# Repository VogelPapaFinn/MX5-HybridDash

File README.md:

# MX5-HybridDash (v2)

A hybrid instrument cluster for a *Mazda MX-5 NB*, which replaces the three small analog gauges and replaces them with 1.5" IPS displays. The project aims to look like an *OEM+* look and feel without destroying the old charm of the car.

## Hardware

The project consists of four custom made PCBs of two types:
- A big Sensor PCB which sits on the back of the cluster, connects to the sensors & ECU and controls the displays
- Three small display PCBs which connect to the displays and receive instructions & data from the Sensor PCB

All four PCBs utilize a powerful ESP32-S3 microcontroller and the CAN bus to communicate with each other. This allows a robust communication without faulty data and provides the possiblity to expand the cluster with new hardware & features in the future-
The displays have a resolution of 360x360 on a 1.5" IPS panel, giving everything a high detailed look.

## Basic Features

Currently the displays can display:
* **RPM**
* **Speed**
* **Indicator (right & left)**
* **Oil Pressure (switch)**
* **Fuel Level**
* **Water Temperature**

This allows for example to calibrate the fuel level sensor so it is more accurate. In my car it shows that the fuel tank is empty when there are 10-15L left. Furthermore due to my size the indicators & the upper scale of the speedometer hide behind the steering wheel. By displaying them in the lower left and right display this isnt an issue anymore.

## Main Feature

My car is a pre-Facelift model and therefore does not have an OBDII connector (at least thats normal here in europe). After a lot of researching, fumbling around, reverse-engineering and testing I managed to establish a **connection** with the **OEM ECU** **without a OBDII connector**. 

At the moment I knowThis of 33 different values that are readable: *(Valus NOT Sensors, as some Sensors output multiple units)*
* **Alternator** - Load (%)
* **Alternator** - Desired Voltage (V)
* **Cabin Fan** - Toggle
* **Brake** - Toggle
* **Rear Window Defroster** - Toggle
* **Daytime Lights** - Toggle
* **Coolant** - Sensor Voltage (V)
* **Coolant** - Temperature (°C)
* **EGR** - Toggle
* **Cooling Fan Speed** - On, Slow Speed
* **Cooling Fan Speed** - On, Medium Speed
* **Cooling Fan Speed** - On, Fast Speed
* **Fuel Pump** - Toggle
* **Injector** - Injection Time (ms)
* **Battery** - Low Voltage (Light Indicator)
* **Headlight Left** - Toggle
* **Headlight Right** - Toggle
* **Idle Bypass** - Time (ms)
* **Idle Switch** - Toggle
* **Engine** - Load (%)
* **Airmass** (V)
* **Airmass** (g/s)
* **Main Relais** - Toggle
* **Engine** - Check Engine Light 
* **Airmass Pre-Cat** - Voltage (V)
* **Power Steering** - Pressure Switch Toggle
* **RPM**
* **EGR** - Valve Position
* **Ignition Timing** - Advancing (°)
* **Immobilizer** - Toggle
* **Throttle** - Voltage (V)
* **ECU** - Input Voltage (V)
* **Speed** (KMH)

## Future Plans
I plan a lot for the project even if its (software wise) stillt at the early beginning. But here is a list of features I aim to implement:
- [ ] Calibration of the sensors
- [ ] Calculation of new Values by combining the hardware & ECU sensors (e.g. current fuel consumption)
- [ ]  Webserver to control the dash
	- [ ] Reading & displaying data from the ECU
- [ ] Customizable display GUI
- [ ] Connection to the smartphone
	- [ ] Google Maps integration / direction notifications in the display GUI
	- [ ] Spotify integration
- [ ] Sensor data tracking & visualization for analyzation (e.g. on track-day use)

Please note that this are just some ideas of mine. This is not a roadmap. This is not organized by priority.

## About me

Hello! Im Finn a 21 year old computer science student from Bonn (Germany). I work as an embedded software engineer (besides my studies of course) and started tinkering around with electronics around two years ago. This project is developed exclusively in my free time for my own fun. I actually started just because I wanted to learn about electronics... Now here I am :)

## Contact

If you have any questions or anything else you are welcome to contact me:
1. Create an issue here in this GitHub repository
2. Contact me via the Miata.net forum. Either via my linked thread or via a [private message](https://forum.miata.net/vb/member.php?u=307577)

## License

The whole project is published under the **GPLv3** license. Basically this means everybody can use, alter and provide the project, free and commercial as long as the provided code and hardware stays open source for the user. Note, that this is my conclusion of the license, before acting please read the license and its terms yourself!!

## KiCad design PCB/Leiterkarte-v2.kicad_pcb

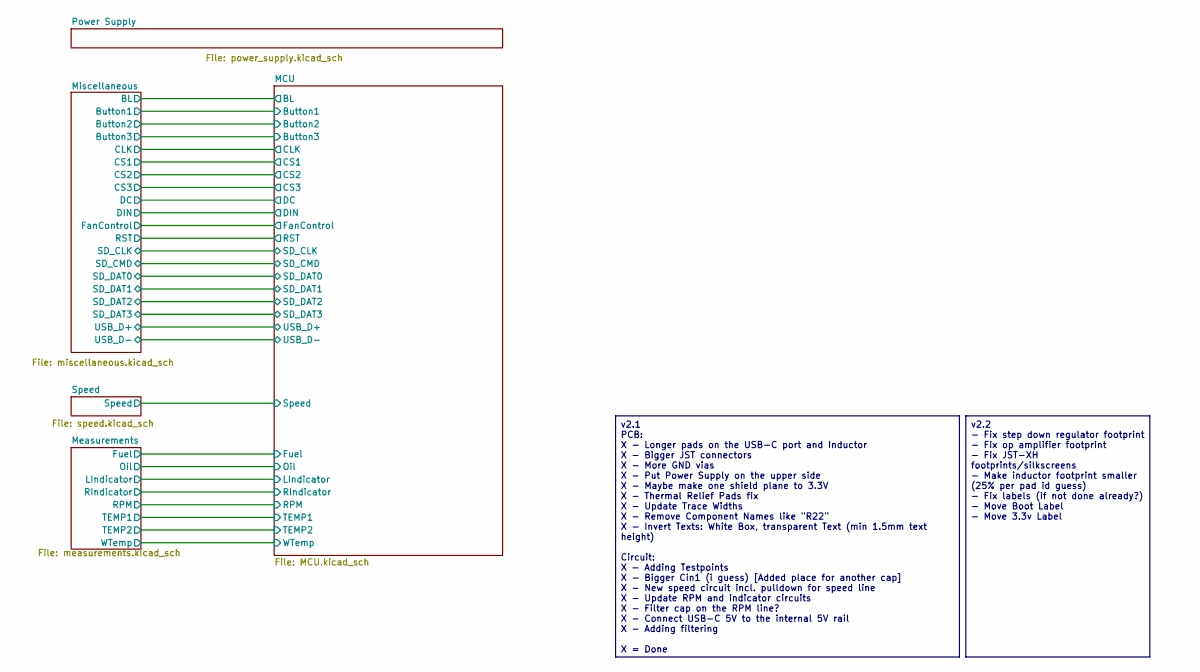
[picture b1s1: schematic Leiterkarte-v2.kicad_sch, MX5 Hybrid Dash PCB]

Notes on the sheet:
v2.2 - Fix step down regulator footprint - Fix op amplifier footprint - Fix JST-XH footprints/silkscreens - Make inductor footprint smaller (25% per pad id guess) - Fix labels (if not done already?) - Move Boot Label - Move 3.3v Label
v2.1 PCB: X - Longer pads on the USB-C port and Inductor X - Bigger JST connectors X - More GND vias X - Put Power Supply on the upper side X - Maybe make one shield plane to 3.3V X - Thermal Relief Pads fix X - Update Trace Widths X - Remove Component Names like "R22" X - Invert Texts: White Box, 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

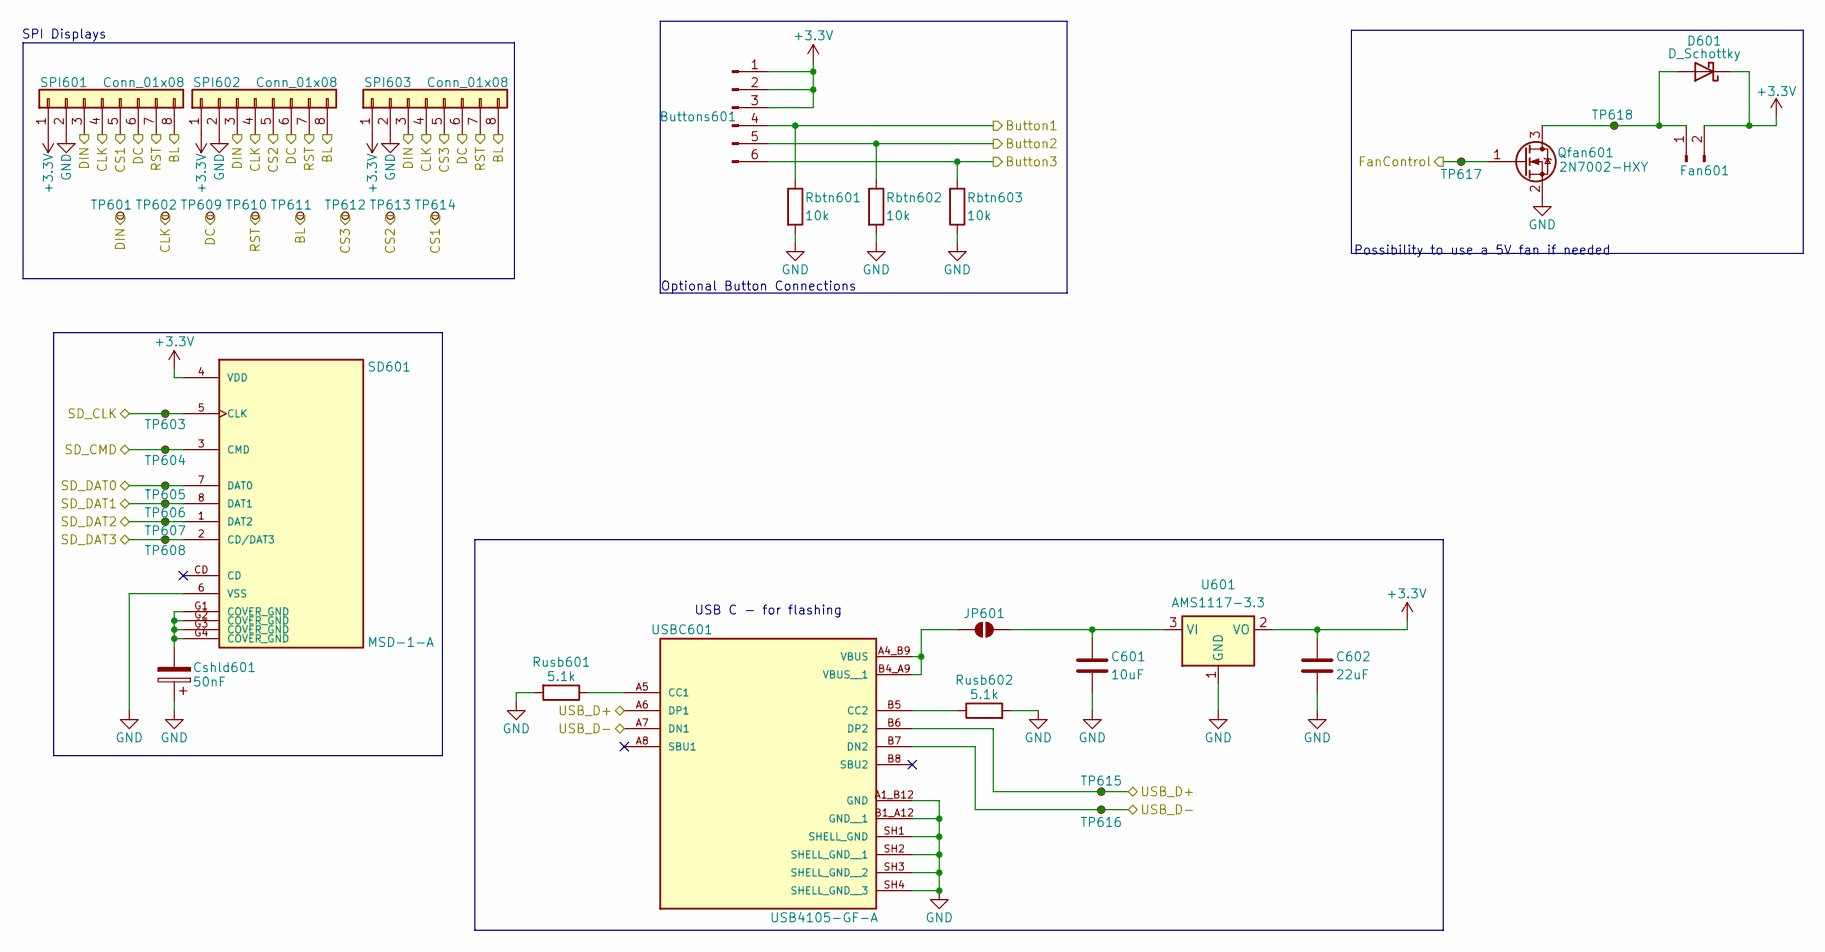
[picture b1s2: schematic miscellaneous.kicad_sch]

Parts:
Buttons601: Conn_01x06_Pin; PinHeader_1x06_P2.54mm_Vertical
C601: 10uF; C_0805_2012Metric
C602: 22uF; C_0805_2012Metric
Cshld601: 50nF; C_0805_2012Metric
D601: D_Schottky; SOD-323HE
Fan601: Conn_01x02_Pin; JST_XH_S2B-XH-A_1x02_P2.50mm_Horizontal
JP601: SolderJumper_2_Open; SolderJumper-2_P1.3mm_Open_TrianglePad1.0x1.5mm
Qfan601: 2N7002-HXY; SOT-23
Rbtn601, Rbtn602, Rbtn603: 10k; R_0603_1608Metric
Rusb601, Rusb602: 5.1k; R_0603_1608Metric
SD601: MSD-1-A; CUI_MSD-1-A; PARTREV 1.0
SPI601, SPI602, SPI603: Conn_01x08; JST_XH_S8B-XH-A_1x08_P2.50mm_Horizontal
TP601, TP602, TP603, TP604, TP605, TP606, TP607, TP608, TP609, TP610, TP611, TP612, TP613, TP614, TP615, TP616, TP617, TP618: TestPoint_Small; TestPoint_Pad_D1.0mm
U601: AMS1117-3.3; SOT-223-3_TabPin2
USBC601: USB4105-GF-A; GCT_USB4105-GF-A; PARTREV B4

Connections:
+3.3V: Buttons601.1, Buttons601.2, Buttons601.3, C602.1, D601.1 (K), Fan601.2, SD601.4 (VDD), SPI601.1, SPI602.1, SPI603.1, U601.2 (VO); also elsewhere on the board
/MCU/BL: SPI601.8, SPI602.8, SPI603.8, TP611.1; also elsewhere on the board
/MCU/Button1: Buttons601.4, Rbtn601.1; also elsewhere on the board
/MCU/Button2: Buttons601.5, Rbtn602.1; also elsewhere on the board
/MCU/Button3: Buttons601.6, Rbtn603.2; also elsewhere on the board
/MCU/CLK: SPI601.4, SPI602.4, SPI603.4, TP602.1; also elsewhere on the board
/MCU/CS1: SPI601.5, TP614.1; also elsewhere on the board
/MCU/CS2: SPI602.5, TP613.1; also elsewhere on the board
/MCU/CS3: SPI603.5, TP612.1; also elsewhere on the board
/MCU/DC: SPI601.6, SPI602.6, SPI603.6, TP609.1; also elsewhere on the board
/MCU/DIN: SPI601.3, SPI602.3, SPI603.3, TP601.1; also elsewhere on the board
/MCU/FanControl: Qfan601.1 (G), TP617.1; also elsewhere on the board
/MCU/RST: SPI601.7, SPI602.7, SPI603.7, TP610.1; also elsewhere on the board
/MCU/SD_CLK: SD601.5 (CLK), TP603.1; also elsewhere on the board
/MCU/SD_CMD: SD601.3 (CMD), TP604.1; also elsewhere on the board
/MCU/SD_DAT0: SD601.7 (DAT0), TP605.1; also elsewhere on the board
/MCU/SD_DAT1: SD601.8 (DAT1), TP606.1; also elsewhere on the board
/MCU/SD_DAT2: SD601.1 (DAT2), TP607.1; also elsewhere on the board
/MCU/SD_DAT3: SD601.2 (CD/DAT3), TP608.1; also elsewhere on the board
/MCU/USB_D+: TP615.1, USBC601.A6 (DP1), USBC601.B6 (DP2); also elsewhere on the board
/MCU/USB_D-: TP616.1, USBC601.A7 (DN1), USBC601.B7 (DN2); also elsewhere on the board
GND: C601.2, C602.2, Cshld601.1, Qfan601.2 (S), Rbtn601.2, Rbtn602.2, Rbtn603.1, Rusb601.2, Rusb602.2, SD601.6 (VSS), SPI601.2, SPI602.2, SPI603.2, U601.1 (GND), USBC601.A1_B12 (GND), USBC601.B1_A12 (GND__1), USBC601.SH1 (SHELL_GND), USBC601.SH2 (SHELL_GND__1), USBC601.SH3 (SHELL_GND__2), USBC601.SH4 (SHELL_GND__3); also elsewhere on the board
unnamed: Cshld601.2, SD601.G1 (COVER_GND), SD601.G2 (COVER_GND), SD601.G3 (COVER_GND), SD601.G4 (COVER_GND)
unnamed: D601.2 (A), Fan601.1, Qfan601.3 (D), TP618.1
unnamed: JP601.1 (A), USBC601.A4_B9 (VBUS), USBC601.B4_A9 (VBUS__1)
unnamed: C601.1, JP601.2 (B), U601.3 (VI)
unnamed: Rusb601.1, USBC601.A5 (CC1)
unnamed: Rusb602.1, USBC601.B5 (CC2)

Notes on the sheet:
SPI Displays
Optional Button Connections
Possibility to use a 5V fan if needed
USB C - for flashing

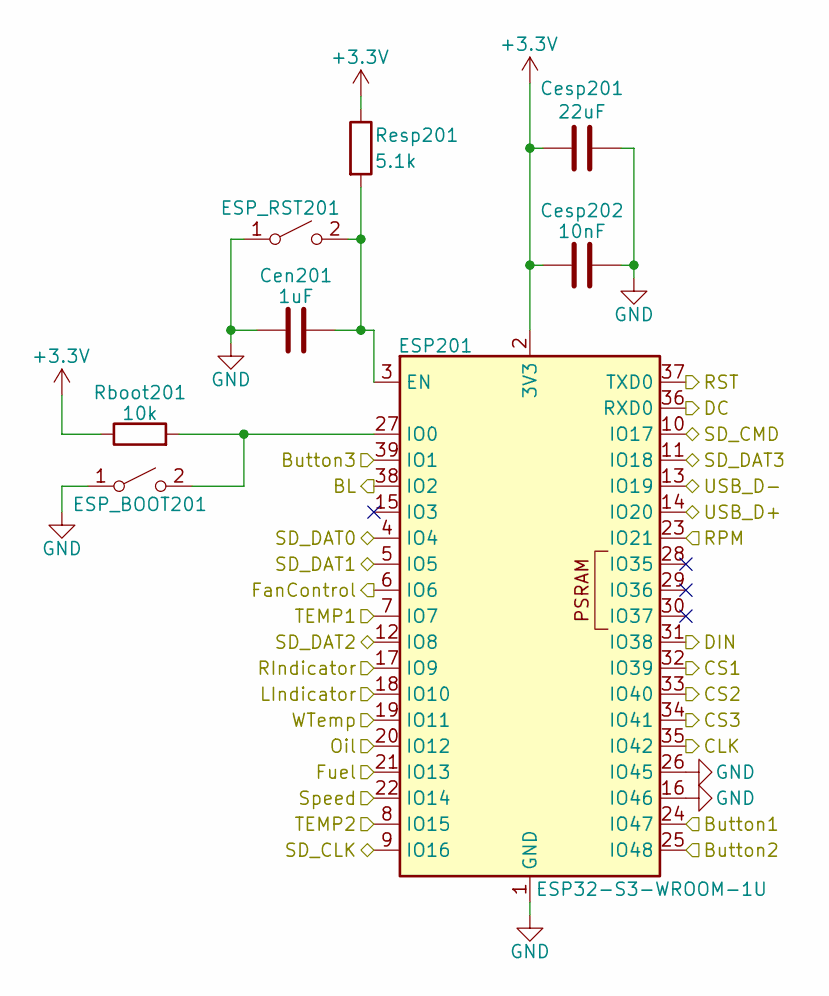
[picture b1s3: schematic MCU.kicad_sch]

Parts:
Cen201: 1uF; C_0805_2012Metric
Cesp201: 22uF; C_0805_2012Metric
Cesp202: 10nF; C_0805_2012Metric
ESP201: ESP32-S3-WROOM-1U
ESP_BOOT201: SW_SPST; small_button
ESP_RST201: SW_SPST; small_button
Rboot201: 10k; R_0603_1608Metric
Resp201: 5.1k; R_0603_1608Metric

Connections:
+3.3V: Cesp201.1, Cesp202.1, ESP201.2 (3V3), Rboot201.1, Resp201.1; also elsewhere on the board
/MCU/BL: ESP201.38 (IO2); also elsewhere on the board
/MCU/Button1: ESP201.24 (IO47); also elsewhere on the board
/MCU/Button2: ESP201.25 (IO48); also elsewhere on the board
/MCU/Button3: ESP201.39 (IO1); also elsewhere on the board
/MCU/CLK: ESP201.35 (IO42); also elsewhere on the board
/MCU/CS1: ESP201.32 (IO39); also elsewhere on the board
/MCU/CS2: ESP201.33 (IO40); also elsewhere on the board
/MCU/CS3: ESP201.34 (IO41); also elsewhere on the board
/MCU/DC: ESP201.36 (RXD0); also elsewhere on the board
/MCU/DIN: ESP201.31 (IO38); also elsewhere on the board
/MCU/FanControl: ESP201.6 (IO6); also elsewhere on the board
/MCU/Fuel: ESP201.21 (IO13); also elsewhere on the board
/MCU/LIndicator: ESP201.18 (IO10); also elsewhere on the board
/MCU/Oil: ESP201.20 (IO12); also elsewhere on the board
/MCU/RIndicator: ESP201.17 (IO9); also elsewhere on the board
/MCU/RPM: ESP201.23 (IO21); also elsewhere on the board
/MCU/RST: ESP201.37 (TXD0); also elsewhere on the board
/MCU/SD_CLK: ESP201.9 (IO16); also elsewhere on the board
/MCU/SD_CMD: ESP201.10 (IO17); also elsewhere on the board
/MCU/SD_DAT0: ESP201.4 (IO4); also elsewhere on the board
/MCU/SD_DAT1: ESP201.5 (IO5); also elsewhere on the board
/MCU/SD_DAT2: ESP201.12 (IO8); also elsewhere on the board
/MCU/SD_DAT3: ESP201.11 (IO18); also elsewhere on the board
/MCU/Speed: ESP201.22 (IO14); also elsewhere on the board
/MCU/TEMP1: ESP201.7 (IO7); also elsewhere on the board
/MCU/TEMP2: ESP201.8 (IO15); also elsewhere on the board
/MCU/USB_D+: ESP201.14 (IO20); also elsewhere on the board
/MCU/USB_D-: ESP201.13 (IO19); also elsewhere on the board
/MCU/WTemp: ESP201.19 (IO11); also elsewhere on the board
GND: Cen201.1, Cesp201.2, Cesp202.2, ESP201.1 (GND), ESP201.16 (IO46), ESP201.26 (IO45), ESP201.40 (GND), ESP201.41 (GND), ESP_BOOT201.1 (A), ESP_RST201.1 (A); also elsewhere on the board
unnamed: Cen201.2, ESP201.3 (EN), ESP_RST201.2 (B), Resp201.2
unnamed: ESP201.27 (IO0), ESP_BOOT201.2 (B), Rboot201.2

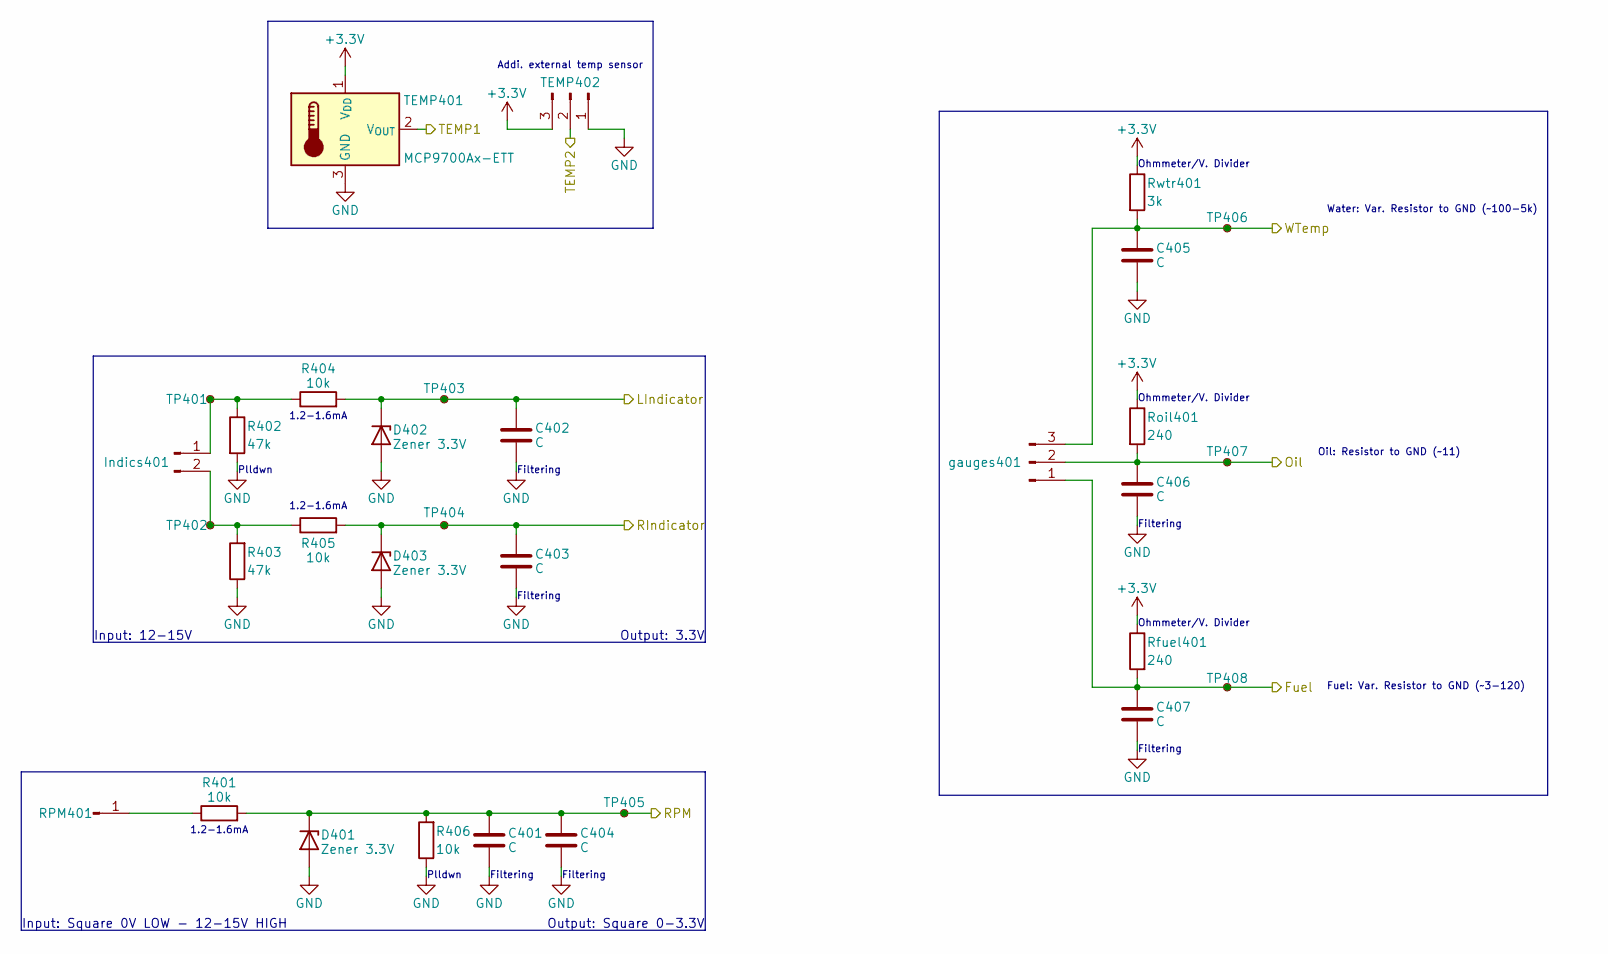
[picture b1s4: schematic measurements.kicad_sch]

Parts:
C401, C402, C403, C404, C405, C406, C407: C; C_0805_2012Metric
D401, D402, D403: Zener 3.3V; D_SOD-123
Indics401: Conn_01x02_Pin; JST_XH_S2B-XH-A_1x02_P2.50mm_Horizontal
R401, R404, R405, R406: 10k; R_0603_1608Metric
R402, R403: 47k; R_0805_2012Metric
RPM401: Conn_01x01_Pin; PinHeader_1x01_P2.54mm_Vertical
Rfuel401: 240; R_0603_1608Metric
Roil401: 240; R_0603_1608Metric
Rwtr401: 3k; R_0603_1608Metric
TEMP401: MCP9700Ax-ETT; SOT-23
TEMP402: Conn_01x03_Pin; JST_XH_S3B-XH-A_1x03_P2.50mm_Horizontal
TP401, TP402, TP403, TP404, TP405, TP406, TP407, TP408: TestPoint_Small; TestPoint_Pad_D1.0mm
gauges401: Conn_01x03_Pin; JST_XH_S3B-XH-A_1x03_P2.50mm_Horizontal

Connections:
+3.3V: Rfuel401.1, Roil401.1, Rwtr401.1, TEMP401.1 (V_{DD}), TEMP402.3; also elsewhere on the board
/MCU/Fuel: C407.1, Rfuel401.2, TP408.1, gauges401.1; also elsewhere on the board
/MCU/LIndicator: C402.1, D402.1 (K), R404.2, TP403.1; also elsewhere on the board
/MCU/Oil: C406.1, Roil401.2, TP407.1, gauges401.2; also elsewhere on the board
/MCU/RIndicator: C403.2, D403.1 (K), R405.2, TP404.1; also elsewhere on the board
/MCU/RPM: C401.2, C404.1, D401.1 (K), R401.2, R406.2, TP405.1; also elsewhere on the board
/MCU/TEMP1: TEMP401.2 (V_{OUT}); also elsewhere on the board
/MCU/TEMP2: TEMP402.2; also elsewhere on the board
/MCU/WTemp: C405.1, Rwtr401.2, TP406.1, gauges401.3; also elsewhere on the board
GND: C401.1, C402.2, C403.1, C404.2, C405.2, C406.2, C407.2, D401.2 (A), D402.2 (A), D403.2 (A), R402.2, R403.1, R406.1, TEMP401.3 (GND), TEMP402.1; also elsewhere on the board
unnamed: Indics401.1, R402.1, R404.1, TP401.1
unnamed: Indics401.2, R403.2, R405.1, TP402.1
unnamed: R401.1, RPM401.1

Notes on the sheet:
Filtering
Addi. external temp sensor
Input: 12-15V
Ohmmeter/V. Divider
Output: 3.3V
Input: Square 0V LOW - 12-15V HIGH
Fuel: Var. Resistor to GND (~3-120)
Plldwn
Water: Var. Resistor to GND (~100-5k)
Oil: Resistor to GND (~11)
Output: Square 0-3.3V
1.2-1.6mA

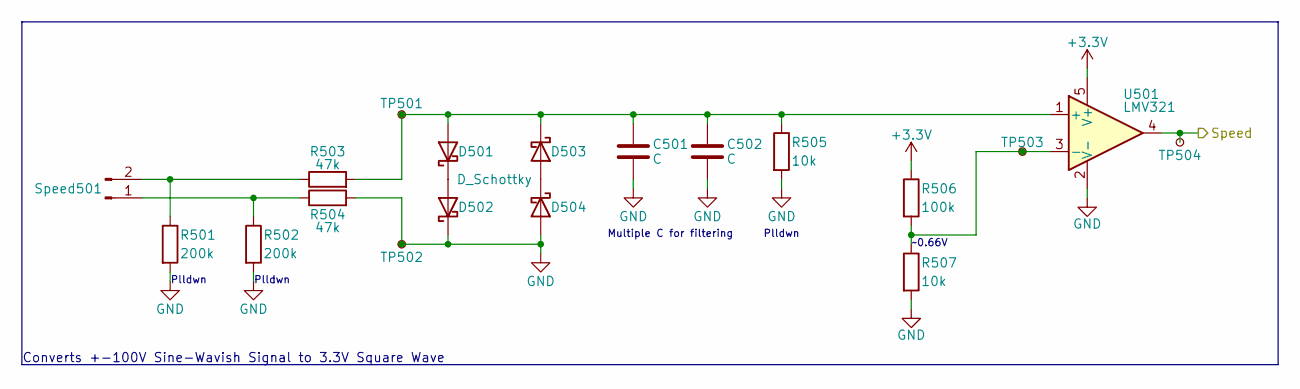
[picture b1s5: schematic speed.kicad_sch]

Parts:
C501, C502: C; C_0805_2012Metric
D501, D502, D503, D504: D_Schottky; SOD-323HE
R501, R502: 200k; R_0805_2012Metric
R503, R504: 47k; R_0805_2012Metric
R505, R507: 10k; R_0603_1608Metric
R506: 100k; R_0603_1608Metric
Speed501: Conn_01x02_Pin; JST_XH_S2B-XH-A_1x02_P2.50mm_Horizontal
TP501, TP502, TP503, TP504: TestPoint_Small; TestPoint_Pad_D1.0mm
U501: LMV321; SOT65P210X110-5N

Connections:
+3.3V: R506.1, U501.5 (V+); also elsewhere on the board
/MCU/Speed: TP504.1, U501.4; also elsewhere on the board
GND: C501.2, C502.2, D502.1 (K), D504.2 (A), R501.2, R502.2, R504.2, R505.2, R507.2, TP502.1, U501.2 (V-); also elsewhere on the board
unnamed: C501.1, C502.1, D501.2 (A), D503.1 (K), R503.2, R505.1, TP501.1, U501.1 (+)
unnamed: D501.1 (K), D502.2 (A)
unnamed: D503.2 (A), D504.1 (K)
unnamed: R502.1, R504.1, Speed501.1
unnamed: R501.1, R503.1, Speed501.2
unnamed: R506.2, R507.1, TP503.1, U501.3 (-)

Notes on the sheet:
Plldwn
Converts +-100V Sine-Wavish Signal to 3.3V Square Wave
~0.66V
Multiple C for filtering

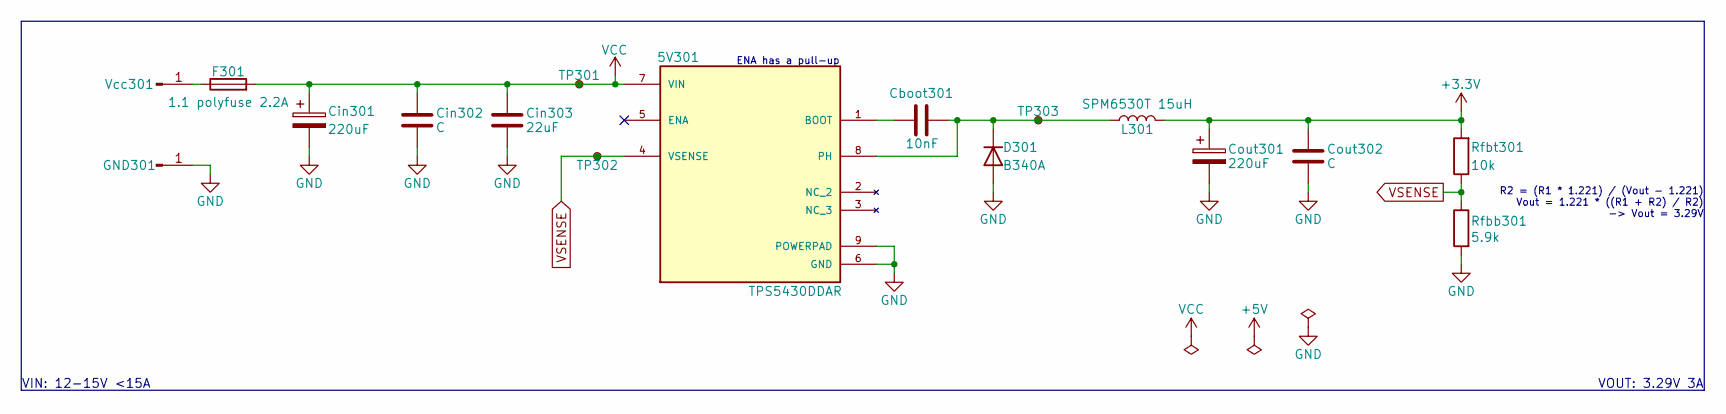
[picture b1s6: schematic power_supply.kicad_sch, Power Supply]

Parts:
5V301: TPS5430DDAR; CONV_TPS5430DDAR; PARTREV I
Cboot301: 10nF; C_0805_2012Metric
Cin301: 220uF; CP_Elec_6.3x7.7
Cin302: C; C_0805_2012Metric
Cin303: 22uF; C_0805_2012Metric
Cout301: 220uF; CP_Elec_6.3x5.9
Cout302: C; C_0805_2012Metric
D301: B340A; D_SMA
F301: 1.1 polyfuse 2.2A; Fuse_1206_3216Metric
GND301: Conn_01x01_Pin; MountingHole_3.2mm_M3_Pad
L301: SPM6530T 15uH; IND_SPM6530T-150M-HZ
Rfbb301: 5.9k; R_0603_1608Metric
Rfbt301: 10k; R_0603_1608Metric
TP301, TP302, TP303: TestPoint_Small; TestPoint_Pad_D1.0mm
Vcc301: Conn_01x01_Pin; MountingHole_3.2mm_M3_Pad

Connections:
+3.3V: Cout301.1, Cout302.2, L301.2, Rfbt301.2; also elsewhere on the board
GND: 5V301.6 (GND), 5V301.9 (POWERPAD), Cin301.2, Cin302.1, Cin303.2, Cout301.2, Cout302.1, D301.2 (A), GND301.1, Rfbb301.2; also elsewhere on the board
unnamed: 5V301.1 (BOOT), Cboot301.2
unnamed: 5V301.8 (PH), Cboot301.1, D301.1 (K), L301.1, TP303.1
unnamed: F301.1, Vcc301.1
VCC: 5V301.7 (VIN), Cin301.1, Cin302.2, Cin303.1, F301.2, TP301.1
VSENSE: 5V301.4 (VSENSE), Rfbb301.1, Rfbt301.1, TP302.1

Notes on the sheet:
VIN: 12-15V <15A
R2 = (R1 * 1.221) / (Vout - 1.221) Vout = 1.221 * ((R1 + R2) / R2) -> Vout = 3.29V
ENA has a pull-up
VOUT: 3.29V 3A

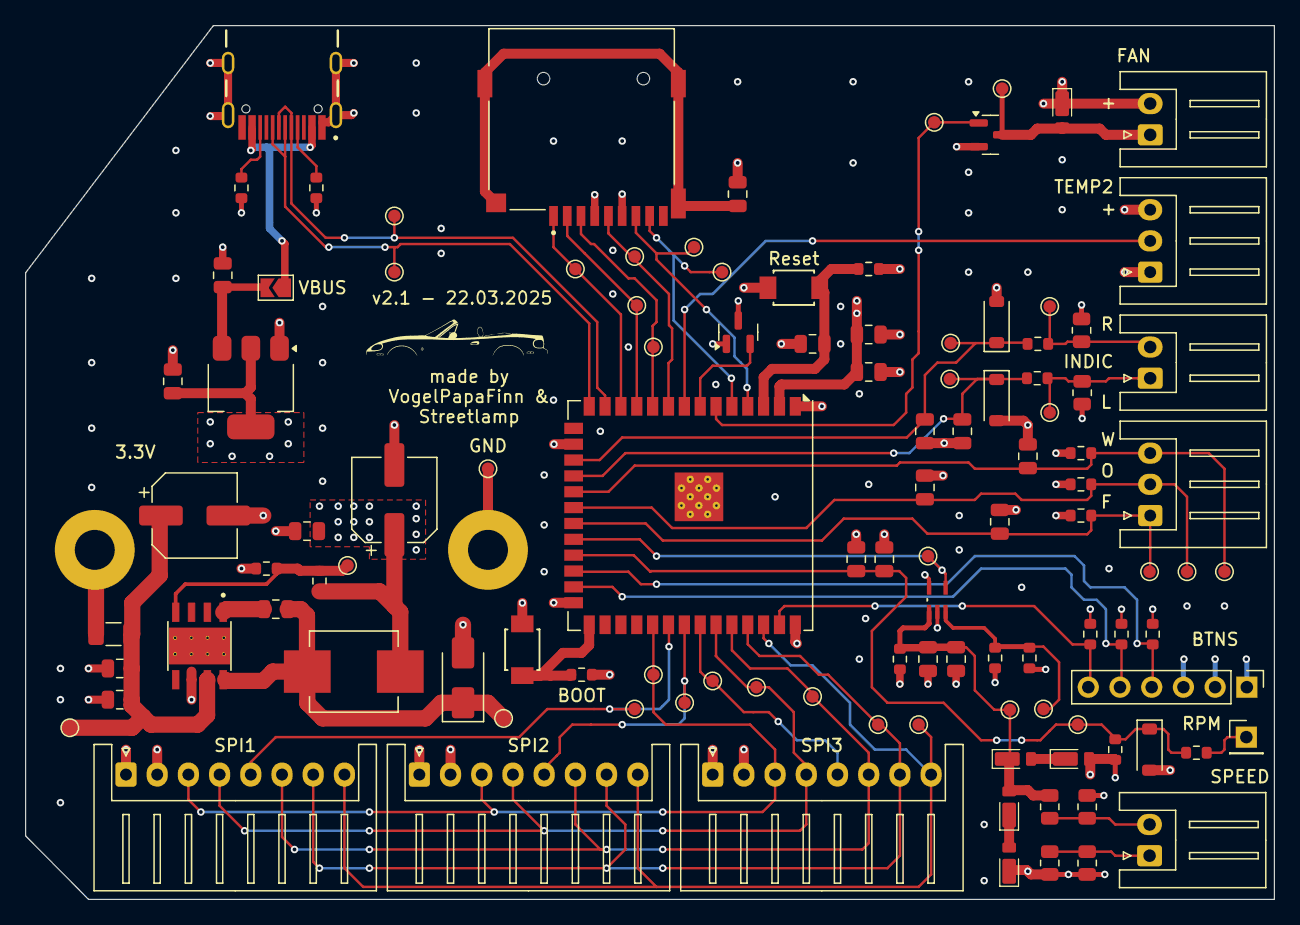
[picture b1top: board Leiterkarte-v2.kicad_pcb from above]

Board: 4 copper layers, 100.0 x 70.0 mm, 113 parts (0 on the bottom side), 53 nets.

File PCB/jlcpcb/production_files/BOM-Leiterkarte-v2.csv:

Comment,Designator,Footprint,LCSC,Quantity
50nF,Cshld601,C_0805_2012Metric,C107156,1
Zener 3.3V,"D401,D402,D403",D_SOD-123,C108453,3
200k,"R501,R502",R_0805_2012Metric,C114562,2
240,"Rfuel401,Roil401",R_0603_1608Metric,C114613,2
47k,"R402,R403,R503,R504",R_0805_2012Metric,C126351,4
3k,Rwtr401,R_0603_1608Metric,C126358,1
MCP9700Ax-ETT,TEMP401,SOT-23,C127949,1
220uF,Cout301,CP_Elec_6.3x5.9,C139569,1
100k,R506,R_0603_1608Metric,C14675,1
5.1k,"Resp201,Rusb601,Rusb602",R_0603_1608Metric,C14677,3
Conn_01x02_Pin,"Fan601,Indics401,Speed501",JST_XH_S2B-XH-A_1x02_P2.50mm_Horizontal,C163035,3
Conn_01x03_Pin,"TEMP402,gauges401",JST_XH_S3B-XH-A_1x03_P2.50mm_Horizontal,C163036,2
USB4105-GF-A,USBC601,GCT_USB4105-GF-A,C2988369,1
ESP32-S3-WROOM-1U,ESP201,ESP32-S3-WROOM-1U,C3013945,1
SPM6530T 15uH,L301,IND_SPM6530T-150M-HZ,C307809,1
22uF,"C602,Cesp201,Cin303",C_0805_2012Metric,C326578,3
AMS1117-3.3,U601,SOT-223-3_TabPin2,C347222,1
Conn_01x06_Pin,Buttons601,PinHeader_1x06_P2.54mm_Vertical,C37208,1
2N7002-HXY,Qfan601,SOT-23,C4748728,1
Conn_01x08,"SPI601,SPI602,SPI603",JST_XH_S8B-XH-A_1x08_P2.50mm_Horizontal,C495697,3
220uF,Cin301,CP_Elec_6.3x7.7,C5246541,1
D_Schottky,"D501,D502,D503,D504,D601",SOD-323HE,C5336764,5
SW_SPST,"ESP_BOOT201,ESP_RST201",small_button,C720477,2
MSD-1-A,SD601,CUI_MSD-1-A,C7529389,1
LMV321,U501,SOT65P210X110-5N,C7972,1
10nF,"Cboot301,Cesp202",C_0805_2012Metric,C83170,2
B340A,D301,D_SMA,C85098,1
5.9k,Rfbb301,R_0603_1608Metric,C862231,1
10uF,C601,C_0805_2012Metric,C89831,1
1uF,Cen201,C_0805_2012Metric,C91186,1
10k,"R401,R404,R405,R406,R505,R507,Rboot201,Rbtn601,Rbtn602,Rbtn603,Rfbt301",R_0603_1608Metric,C98220,11
TPS5430DDAR,5V301,CONV_TPS5430DDAR,C9864,1
1.1 polyfuse 2.2A,F301,Fuse_1206_3216Metric,C7542962,1

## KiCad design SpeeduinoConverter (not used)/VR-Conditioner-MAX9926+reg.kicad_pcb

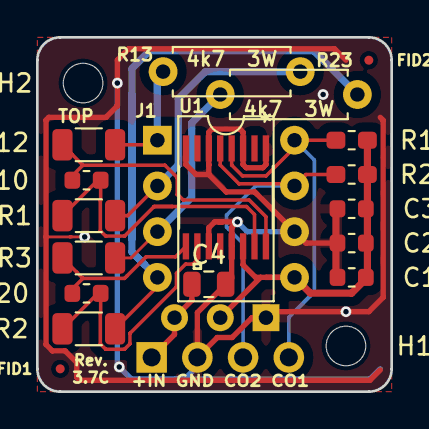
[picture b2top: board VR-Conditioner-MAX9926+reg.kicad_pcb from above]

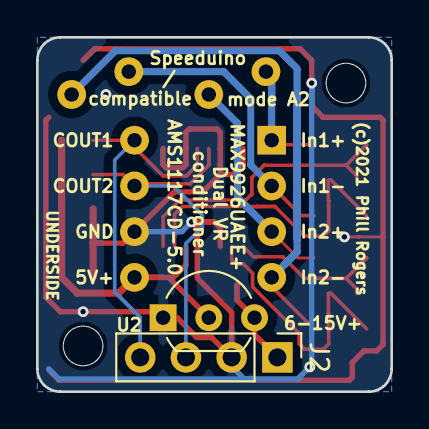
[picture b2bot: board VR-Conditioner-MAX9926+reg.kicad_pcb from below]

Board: 2 copper layers, 19.7 x 19.7 mm, 22 parts (2 on the bottom side), 13 nets.

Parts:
C1: 10n; C_0603_1608Metric
C2: 100n; C_0603_1608Metric
C3: 1u; C_0603_1608Metric
C4: 10u; C_0805_2012Metric
C10, C20: 1n; C_0603_1608Metric
FID1, FID2: Fiducial; Fiducial_0.5mm_Mask1mm
H1, H2: MountingHole; MountingHole_2.2mm_M2
J1: 8-pin header; DIP-8_W7.62mm
J2: Edge; PinHeader_1x04_P2.54mm_Vertical
R1, R2, R3, R12: 10k; R_1206_3216Metric
R10, R20: 1k; R_0603_1608Metric_Pad1.05x0.95mm_HandSolder
R13, R23: 4.7k; R_Axial_DIN0207_L6.3mm_D2.5mm_P7.62mm_Horizontal
U1: MAX9926UAEE+; MAX9926UAEE&plus_
U2: AMS1117CD-5.0; TO-92_Inline_Wide

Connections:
+12V: C4.1, J2.1, U2.3 (VI)
/COUT1: J1.8, J2.4, R10.2, U1.4 (COUT1)
/COUT2: J1.7, J2.3, R20.2, U1.5 (COUT2)
GND: C1.2, C2.2, C3.2, C4.2, J1.6, J2.2, U1.1 (INT_THRS1), U1.3 (BIAS1), U1.6 (BIAS2), U1.8 (INT_THRS2), U1.11 (GND), U1.13 (ZERO_EN), U2.1 (GND)
unnamed: J1.1, R12.2, R13.1
unnamed: J1.2, R1.2, R13.2
unnamed: J1.3, R3.2, R23.1
unnamed: J1.4, R2.2, R23.2
unnamed: C10.1, R12.1, U1.16 (IN1+)
unnamed: C10.2, R1.1, U1.15 (IN1-)
unnamed: C20.2, R3.1, U1.9 (IN2+)
unnamed: C20.1, R2.1, U1.10 (IN2-)
VCC: C1.1, C2.1, C3.1, J1.5, R10.1, R20.1, U1.14 (VCC), U2.2 (VO)

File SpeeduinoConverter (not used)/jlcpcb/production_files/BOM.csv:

Comment,Designator,Footprint,LCSC
10n,C1,C_0603_1608Metric,
100n,C2,C_0603_1608Metric,
1u,C3,C_0603_1608Metric,
10u,C4,C_0805_2012Metric,
1n,C10,C_0603_1608Metric,
1n,C20,C_0603_1608Metric,
10k,R3,R_1206_3216Metric,
10k,R2,R_1206_3216Metric,
10k,R1,R_1206_3216Metric,
Fiducial,FID1,Fiducial_0.5mm_Mask1mm,
Fiducial,FID2,Fiducial_0.5mm_Mask1mm,
8-pin header,J1,DIP-8_W7.62mm,
1k,R10,R_0603_1608Metric_Pad1.05x0.95mm_HandSolder,
1k,R20,R_0603_1608Metric_Pad1.05x0.95mm_HandSolder,
MAX9926UAEE+,U1,MAX9926UAEE&plus_,
4.7k,R13,R_Axial_DIN0207_L6.3mm_D2.5mm_P7.62mm_Horizontal,
4.7k,R23,R_Axial_DIN0207_L6.3mm_D2.5mm_P7.62mm_Horizontal,
MountingHole,H1,MountingHole_2.2mm_M2,
MountingHole,H2,MountingHole_2.2mm_M2,
10k,R12,R_1206_3216Metric,
Edge,J2,PinHeader_1x04_P2.54mm_Vertical,
AMS1117CD-5.0,U2,TO-92_Inline_Wide,

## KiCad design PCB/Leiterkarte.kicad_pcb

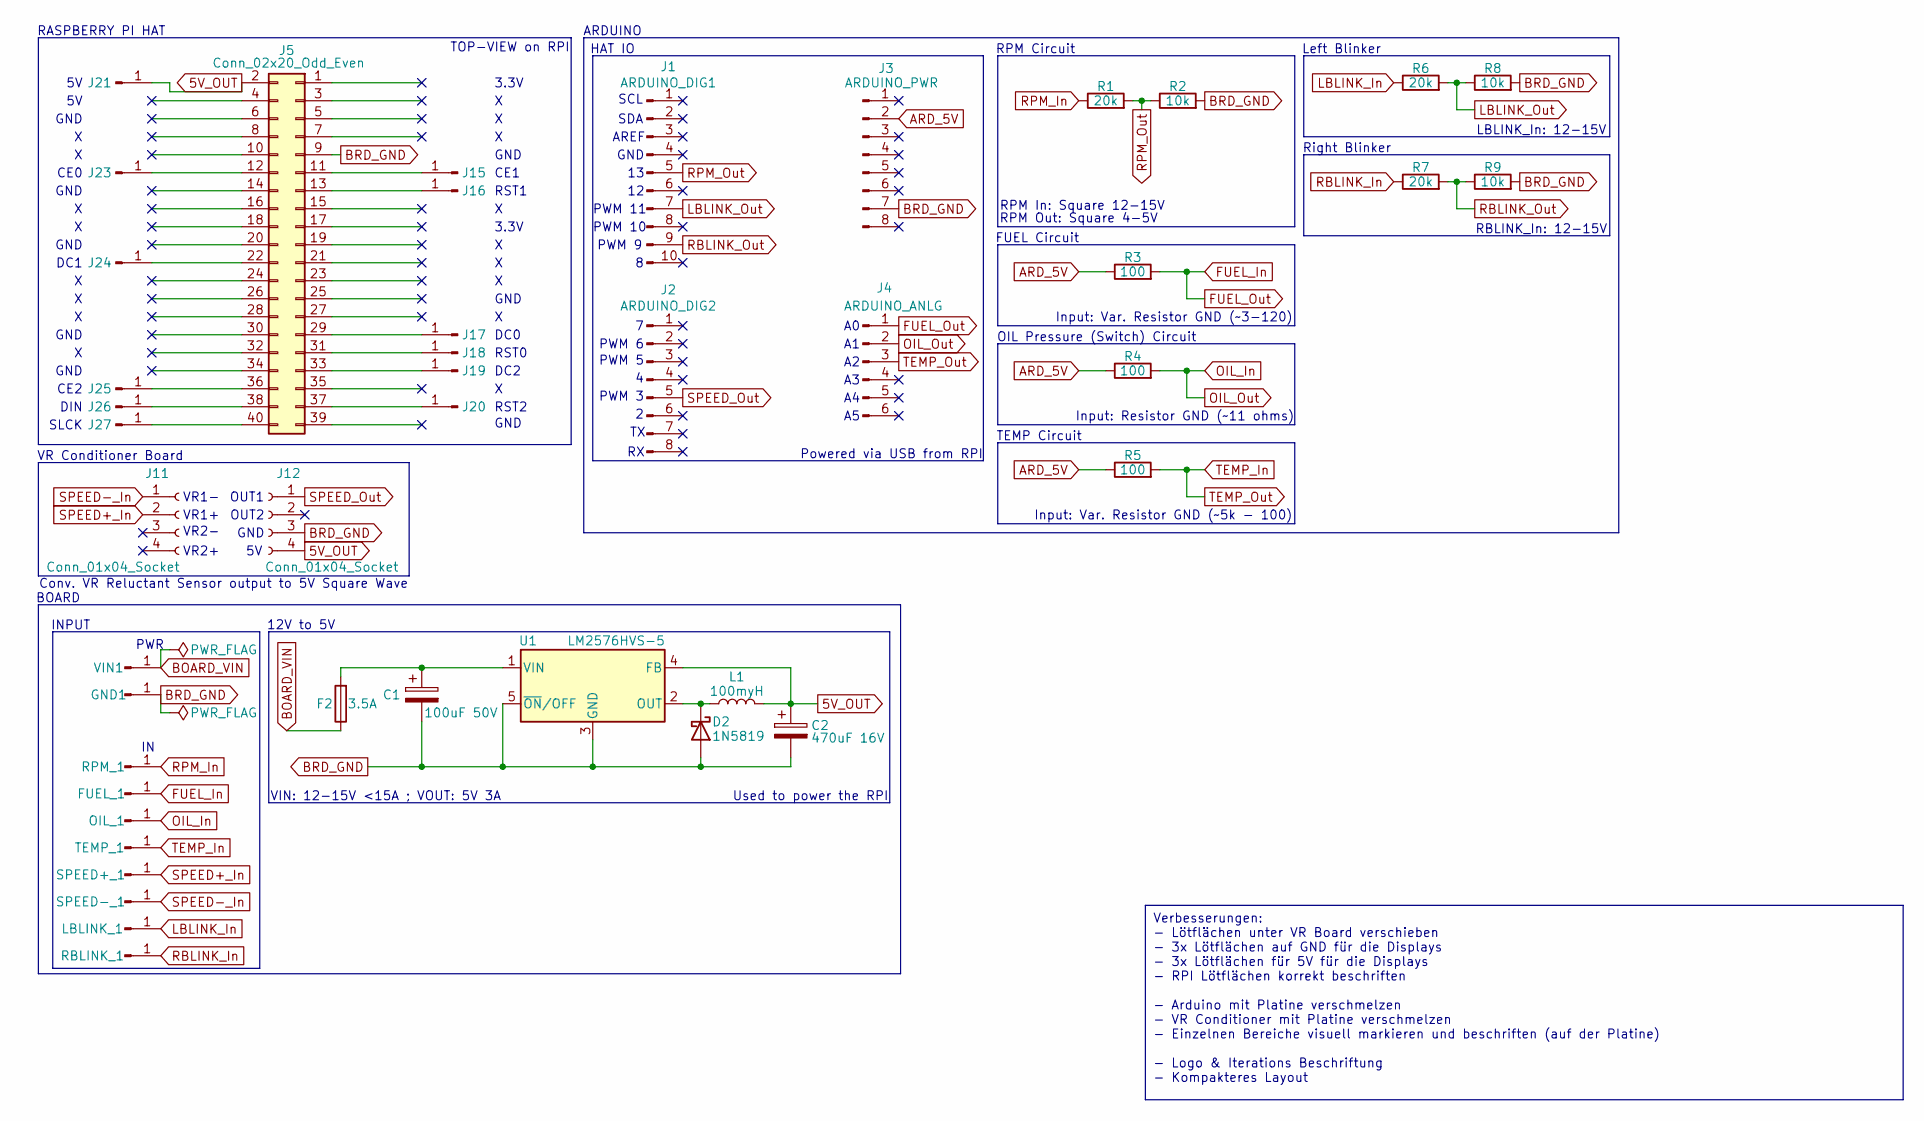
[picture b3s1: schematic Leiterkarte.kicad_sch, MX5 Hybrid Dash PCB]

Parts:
C1: 100uF 50V; CP_Elec_8x10.5
C2: 470uF 16V; CP_Elec_8x10.5
D2: 1N5819; D_DO-27_P12.70mm_Horizontal
F2: 3.5A; Fuse_Bourns_MF-SM_7.98x5.44mm
FUEL_1: Conn_01x01_Pin; SolderWire-0.75sqmm_1x01_D1.25mm_OD3.5mm
GND1: Conn_01x01_Pin; SolderWire-0.75sqmm_1x01_D1.25mm_OD3.5mm
J1: ARDUINO_DIG1; PinHeader_1x10_P2.54mm_Vertical
J2: ARDUINO_DIG2; PinHeader_1x08_P2.54mm_Vertical
J3: ARDUINO_PWR; PinHeader_1x08_P2.54mm_Vertical
J4: ARDUINO_ANLG; PinHeader_1x06_P2.54mm_Vertical
J5: Conn_02x20_Odd_Even; PinSocket_2x20_P2.54mm_Vertical
J11, J12: Conn_01x04_Socket; PinSocket_1x04_P2.54mm_Vertical
J15, J16, J17, J18, J19, J20, J21, J23, J24, J25, J26, J27: Conn_01x01_Pin; SolderWire-0.75sqmm_1x01_D1.25mm_OD3.5mm
L1: 100myH; L_12x12mm_H8mm
LBLINK_1: Conn_01x01_Pin; SolderWire-0.75sqmm_1x01_D1.25mm_OD3.5mm
OIL_1: Conn_01x01_Pin; SolderWire-0.75sqmm_1x01_D1.25mm_OD3.5mm
R1, R6, R7: 20k; R_0805_2012Metric
R2, R8, R9: 10k; R_0805_2012Metric
R3, R4, R5: 100; R_0805_2012Metric
RBLINK_1: Conn_01x01_Pin; SolderWire-0.75sqmm_1x01_D1.25mm_OD3.5mm
RPM_1: Conn_01x01_Pin; SolderWire-0.75sqmm_1x01_D1.25mm_OD3.5mm
SPEED+_1: Conn_01x01_Pin; SolderWire-0.75sqmm_1x01_D1.25mm_OD3.5mm
SPEED-_1: Conn_01x01_Pin; SolderWire-0.75sqmm_1x01_D1.25mm_OD3.5mm
TEMP_1: Conn_01x01_Pin; SolderWire-0.75sqmm_1x01_D1.25mm_OD3.5mm
U1: LM2576HVS-5; TO-263-5_TabPin3
VIN1: Conn_01x01_Pin; SolderWire-0.75sqmm_1x01_D1.25mm_OD3.5mm

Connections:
5V_OUT: C2.1, J5.2, J12.4, J21.1, L1.2, U1.4 (FB)
ARD_5V: J3.2, R3.1, R4.1, R5.1
BOARD_VIN: F2.1, VIN1.1
BRD_GND: C1.2, C2.2, D2.2 (A), GND1.1, J3.7, J5.9, J12.3, R2.2, R8.2, R9.2, U1.3 (GND), U1.5 (~ON/OFF)
FUEL_In: FUEL_1.1, J4.1, R3.2
LBLINK_In: LBLINK_1.1, R6.1
LBLINK_Out: J1.7, R6.2, R8.1
unnamed: D2.1 (K), L1.1, U1.2 (OUT)
unnamed: J5.11, J15.1
unnamed: J5.13, J16.1
unnamed: J5.29, J17.1
unnamed: J5.31, J18.1
unnamed: J5.33, J19.1
unnamed: J5.37, J20.1
unnamed: J5.12, J23.1
unnamed: J5.22, J24.1
unnamed: J5.36, J25.1
unnamed: J5.38, J26.1
unnamed: J5.40, J27.1
unnamed: C1.1, F2.2, U1.1 (VIN)
OIL_In: J4.2, OIL_1.1, R4.2
RBLINK_In: R7.1, RBLINK_1.1
RBLINK_Out: J1.9, R7.2, R9.1
RPM_In: R1.1, RPM_1.1
RPM_Out: J1.5, R1.2, R2.1
SPEED+_In: J11.2, SPEED+_1.1
SPEED-_In: J11.1, SPEED-_1.1
SPEED_Out: J2.5, J12.1
TEMP_In: J4.3, R5.2, TEMP_1.1

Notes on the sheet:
Verbesserungen: - Lötflächen unter VR Board verschieben - 3x Lötflächen auf GND für die Displays - 3x Lötflächen für 5V für die Displays - RPI Lötflächen korrekt beschriften - Arduino mit Platine verschmelzen - VR Conditioner mit Platine verschmelzen - Einzelnen Bereiche visuell markieren und besch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
RST2
RPM In: Square 12-15V
FUEL Circuit
TEMP Circuit
GND
SDA
PWM 10
CE2
OIL Pressure (Switch) Circuit
PWM 3
RST0
12V to 5V
OUT2
PWM 6
Input: Var. Resistor GND (~5k - 100)
Powered via USB from RPI
DC1
SCL
ARDUINO
SLCK
BOARD
Left Blinker
PWM 11
DC0
3.3V
DC2
HAT IO
VR2-
OUT1
AREF
RPM Out: Square 4-5V
RBLINK_In: 12-15V
Input: Resistor GND (~11 ohms)
Input: Var. Resistor GND (~3-120)
LBLINK_In: 12-15V
PWM 5
TOP-VIEW on RPI
CE1
VR2+

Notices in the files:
SpeeduinoConverter (not used)/VR-Conditioner-MAX9926+reg.kicad_pcb:
(c)2021 Phill Rogers @ TechColab.co.je
parts and their libraries:
Copyright 2016 Accelerated Designs. All rights reserved.
